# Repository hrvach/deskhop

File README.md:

# DeskHop - Fast Desktop Switching

Did you ever notice how, in the crazy world of tech, there's always that one quirky little project trying to solve a problem so niche that its only competitors might be a left-handed screwdriver and a self-hiding alarm clock?

I use two different computers in my daily workflow and share a single keyboard/mouse pair between them. Trying several USB switching boxes found on Amazon made me realize they all suffer from similar issues - it takes a while to switch, the process is quite clumsy when trying to find the button and frankly, it just doesn't get any better with time.

All I wanted was a way to use a keyboard shortcut to quickly switch outputs, paired with the ability to do the same by magically moving the mouse pointer between monitors. This project enables you to do both, even if your computers run different operating systems!

## Features

- Completely **[free and open source](https://certification.oshwa.org/de000149.html)**
- No noticeable delay when switching
- Simply drag the mouse pointer between computers
- No software installed
- Affordable and obtainable components (<15€)
- 3D printable snap-fit case
- Full Galvanic isolation between your outputs
- Works with Linux, macOS and Windows

[User Manual](misc/user-manual.pdf) is now available

------

## How it works

The device acts as an intermediary between your keyboard/mouse and the computer, establishing and maintaining connections with both computers at once. Then it chooses where to forward your mouse and keystrokes to, depending on your selection. Keyboard follows the mouse and vice versa, so just dragging the mouse to the other desktop will switch both.

## Mouse

To get the mouse cursor to magically jump across, the mouse hid report descriptor was changed to use absolute coordinates and then the mouse reports (that still come in relative movements) accumulate internally, keeping the accurate tally on the position.

When you try to leave the monitor area in the direction of the other monitor, it keeps the Y coordinate and swaps the maximum X for a minimum X, then flips the outputs. This ensures that the cursor seamlessly appears at the same height on the other monitor, enhancing the perception of a smooth transition.

<p align="center"> Dragging the mouse from Mac to Linux automatically switches outputs. </p>

------

The actual switch happens at the very moment when one arrow stops moving and the other one starts.

## Keyboard

Acting as a USB Host and querying your keyboard periodically, it looks for a preconfigured hotkey in the hid report (usually Ctrl + Caps Lock for me). When found, it will forward all subsequent characters to the other output.

To have a visual indication which output you are using at any given moment, you can repurpose keyboard LEDs and have them provide the necessary feedback.

It also remembers the LED state for each computer, so you can pick up exactly how you left it.

## How to build

To avoid version mismatch and reported path issues when building, as well as to save you from having to download a large SDK, the project now bundles minimal pico sdk and tinyusb.

On a Debian/Ubuntu systems, make sure to install these:

```shell
apt update
apt install \
    build-essential \
    cmake \
    gcc-arm-none-eabi \
    libnewlib-arm-none-eabi \
    python3
```

You should be able to build by running:

```shell
cmake -S . -B build
cmake --build build
```

additionally, to rebuild web UI check webconfig/ and execute ```./render.py```, you'll need jinja2 installed.

An alternative can be to use docker via 'docker compose' or 'docker-compose':
```
docker-compose -f misc/docker.yml run --rm build_container
```
This ensures reproducible builds.

To rebuild the disk, check disk/ folder and run ```./create.sh```, tweak to your system if needed. You'll need **dosfstools** (to provide mkdosfs),

## Using a pre-built image

Alternatively, you can use the [pre-built images](https://github.com/hrvach/deskhop/releases). Since version 0.6 there is only a single universal image. You need the .uf2 file which you simply copy to the device in one of the following ways:

## Upgrading firmware

**Option 1** - (firmware 0.6 and later) Put the device in "config mode" by simultaneously pressing **left ctrl + right shift + c + o**. Device your keyboard is plugged into will reboot and turn into a USB drive called "DESKHOP". All you need to do is copy the .uf2 file to it. Once image is verified, device will flash and reboot, then proceed to upgrade the other board. During this operation the led will blink. Once it's done, it will write flash and reboot, completing the operation.

_Note_ - This is not an actual generic USB drive, you can't use it to copy files to it.

**Option 2** - Using the ROM bootloader - hold the on-board button while connecting each Pico and copy the uf2 to the flash drive that appears. Images later than 0.6 support holding the button without having to fiddle around the power supply, but the "hold button while plugging" should always work, regardless of device state.

**Option 3** - CDC Flash Command (Debug builds only) - If the firmware was built with `DH_DEBUG_CDC_FLASH=ON`, you can trigger bootloader mode via CDC serial command:
```shell
echo -n 'flash' > /dev/tty.usbmodem11104
```
This immediately resets the device into bootloader mode where it appears as "RPI-RP2" drive. This feature is intended for development workflows.

## Misc features

### Mouse slowdown

Ever tried to move that YT video slider to a specific position but your mouse moves too jumpy and suddenly you are moving your hand super-carefully like you're 5 and playing "Operation" all over again?

**Press right CTRL + right ALT** to toggle a slow-mouse mode. The mouse pointer will slow down considerably, enabling you to get the finer precision work done and still have your mouse moving normally by quickly pressing the same keys again.

### Switch Lock

If you want to lock yourself to one screen, use ```RIGHT CTRL + K```.
This will make sure you won't accidentally leave your current screen. To turn off, press the same key combo again.

### Wrap Around

**Off by default**, turned on with the Wrap Around checkbox in the web config. Pushing the mouse past the outer edge of your outermost screen takes it to the far edge of the other computer's outermost screen, so you can keep moving in one direction and cycle between the two. The jump threshold applies here too. On Windows with more than one screen, the wrap only meets the far edge with acceleration off, Windows at its default pointer speed without Enhance pointer precision, Speed X at 32767 divided by the screen width (rounded down) and Speed Y at 32767 divided by the height.

### Lock Both Screens

You can lock both computers at once by using ```RIGHT CTRL + L```.
To make use of this feature, first set up the OS for each output in config (since the shortcuts are different).

### Gaming Mode

If you're gaming, there is a chance your game might not work properly with absolute mouse mode. To address that issue, a **gaming mode** is introduced, toggled by ```LEFT CTRL + RIGHT SHIFT + G```. When in gaming mode, you are locked to the current screen and your mouse behaves like a standard relative mouse. This should also fix various virtual machine issues, currently unsupported operating systems etc.

### Screensaver

Supposedly built in to prevent computer from entering standby, but truth be told - it is just fun to watch. **Off by default**, will make your mouse pointer bounce around the screen like a Pong ball. When enabled, it activates after a period of inactivity defined in user config header and automatically switches off as soon as you send any output towards that screen.

Potential usage example - I have a buggy USB dock that won't resume video from standby, so not allowing it to sleep can be a handy workaround.

## Hardware

[The circuit](schematics/DeskHop_v1.1.pdf) is based on two Raspberry Pi Pico boards, chosen because they are cheap (4.10 € / pc), can be hand soldered and most suppliers have them in stock.

The Picos are connected using UART and separated by an Analog Devices ADuM1201 dual-channel digital isolator (~3€) or a much cheaper, faster and pin-compatible TI ISO7721DR (~1.5€) which is the preferred choice.

While they normally don't have support for dual USB, thanks to an [amazing project](https://github.com/sekigon-gonnoc/Pico-PIO-USB) where USB is implemented using the programmable IO wizardry found in RP2040, there is support for it to act both as an USB host and device.

## PCB [updated]

To keep things as simple as possible for DIY builds, the traces were kept on one side and the number of parts kept to a minimum.

USB D+/D- differential lines should be identical in length, but they are slightly asymmetrical on purpose to counter the length difference on the corresponding GPIO traces PICO PCB itself, so the overall lengths should match.

Zd (differential impedance) is aimed as 90 ohm (managed to get ~107, close enough :)).

The thickness is designed to be 1.6 mm for snap-fit to work as expected.

There are 2 versions of the PCB (no major differences for the user). Original (v1.0) is easier to solder and assemble, while v1.1 offers some upgrades like:

- added ESD protection (TPD4E1U06DBVR)
- added VBUS capacitor for the keyboard/mouse connectors
- silkscreen orientation markings
- holes for clone boards with headers pre-soldered and easier alignment
- USB 27 ohm resistors

  This version is slightly more difficult to hand solder due to the small transient voltage suppressor IC and 0805 resistors, but it's totally doable. TVS can in theory be omitted (not advised) and it will still work.

Upcoming - board with bare rp2040s that doesn't need Picos, is smaller and more convenient.

## Case

Since I'm not very good with 3d, the case is [simple and basic](case/) but does the job. It should be easy to print, uses ~33g of filament and takes a couple of hours.

Horizontal PCB movements are countered by pegs sliding through holes and vertical movements by snap-fit lugs on the sides - no screws required. The case was given a slight redesign to feature the logo and two additional snap-fit lugs, so it provides a better seal.

Micro USB connectors on both boards are offset from the side of the case, so slightly larger holes should allow for cables to reach in.

The lid is of a snap-fit design, with a screwdriver slot for opening. The markings on top are recessed and can be finished with e.g. crayons to give better contrast (or simply left as-is).

## Bill of materials

<details closed>
  <summary>Click here to view original PCB v1.0 BOM</summary>

| Component          | Qty | Unit Price / € | Price / €|
|--------------------|-----|----------------|----------|
| Raspberry Pi Pico  | 2   | 4.10           | 8.20     |
| ADuM1201BRZ        | 1   | 2.59           | 2.59     |
| Cap 1206 SMD 100nF | 2   | 0.09           | 0.18     |
| USB-A PCB conn.    | 2   | 0.20           | 0.40     |
| Headers 2.54 1x03  | 2   | 0.08           | 0.16     |
|                    |     |                |          |
|                    |     |          Total | 11.53    |

TI ISO7721DR can be used instead of the ADuM - it's pin-compatible, much cheaper and with better specs.

</details>

### PCB v1.1

| Component      | Part                | Qty | Unit Price / € | Price / €|
|----------------|---------------------|-----|----------------|----------|
|     U1, U2     | Raspberry Pi Pico   | 2   | 4.10           | 8.20     |
|     J1, J4     | USB-A PCB conn.     | 2   | 0.20           | 0.40     |
|       U4       | TI ISO7721DR        | 1   | 1.40           | 1.40     |
|                | (**OR** ADuM1201BRZ)|     |                |          |
|     C1, C2     | Cap 0805 SMD 100nF  | 2   | 0.09           | 0.18     |
| R1, R2, R3, R4 | Res 0805 SMD 27ohm  | 4   | 0.03           | 0.12     |
|     U3, U5     | TPD4E1U06DBVR       | 2   | 0.31           | 0.62     |
|     C3, C4     | Cap 4.7uF SMD 0805  | 2   | 0.07           | 0.14     |
|     J2, J3     | Headers 2.54 1x03   | 2   | 0.08           | 0.16     |
|                |                     |     |                |          |
|                |                     |     |          Total | 11.22    |

USB-A connector can be Molex MX-67643-0910 or a cheaper/budget one that shares the same dimensions.

Additional steps:

- making the PCB ([Gerber provided](pcb/), choose 1.6 mm thickness)
- 3d printing the case ([stl files provided](case/), ~33g filament)

## Assembly guide

If you have some experience with electronics, you don't need this. However, some of you might not, and in that case this video might help guide you through the process. Please note, after soldering you should clean the flux from the PCB to prevent corrosion.

The standard process to do that is using isopropyl alcohol and an old toothbrush. But guess what? I'm not putting my old toothbrush online, so you'll just have to improvise that part :)

[NOTE] The video assembly guide covers pcb v1.0. The revised version is very similar and the procedure is basically the same.

## Usage guide

### Keyboard shortcuts - (fw versions 0.68+)

_Config_:

- ~~```Left Shift```~~ ```Left Ctrl + Right Shift + C + O``` - enter config mode
- ```Right Shift + F12 + D``` - remove flash config
- ```Right Shift + F12 + Y``` - save screen switch offset

_Usage_:

- ```Right CTRL + Right ALT``` - Toggle slower mouse mode
- ```Right CTRL + K``` - Lock/Unlock mouse desktop switching
- ```Right CTRL + L``` - Lock both outputs at once (set output OS before, see shortcuts below)
- ~~```Left Shift```~~ ```Left CTRL + Right Shift + G``` - Toggle gaming mode (lock to screen, act as standard mouse)
- ```Left CTRL + Right Shift + S``` - Enable screensaver
- ```Left CTRL + Right Shift + X``` - Disable screensaver
- ```Left CTRL + Caps Lock``` - Switch between outputs

Note: some keyboards don't send both shifts at the same time properly, that's why the shortcut was changed - to work for everyone. Apologies for the confusion.

### Switch cursor height calibration

This step is not required, but it can be handy if your screens are not perfectly aligned or differ in size. The objective is to have the mouse pointer come out at exactly the same height.

Just park your mouse on the LARGER screen at the height of the smaller/lower screen (illustrated) and press ```Right Shift + F12 + Y```. Your LED (and caps lock) should flash in confirmation.

Repeat for the bottom border (if it's above the larger screen's border). This will get saved to flash and it should keep this calibration value from now on.

### Multiple screens per output

Windows and Mac have issues with multiple screens and absolute positioning, so workarounds are needed (still experimental). There is a better workaround under construction, but for now you have to set the operating system for each output and number of screens.

Your main screens need to be in the middle, and secondary screen(s) on the edges. To configure the actual options, open the web configuration page for your device.

### Web configuration mode

Starting with fw 0.6, an improved configuration mode is introduced. To configure your device, follow these instructions:

1. Press Left Ctrl + Right Shift + C + O - your device will reboot and enter configuration mode (on the side your keyboard is plugged into). LED will keep blinking during the configuration session.

1. A new USB drive will appear named "DESKHOP" with a single file, config.htm

1. Open that file with Chromium / Chrome. Unfortunately FF is not supported right now, since they avoid implementing WebHID.

1. Click connect and allow deskhop device to pair.

1. Configure the options as you wish and click save to write to device.

1. Click "exit" in the menu to leave configuration mode for added safety.

<details closed>
  <summary>Linux doesn't see device? Click here.</summary>

**Q**: Chromium on Linux doesn't work.

**A**: You probably need to tweak /dev permissions or create a corresponding udev rules file and make sure your user is in the right group, like so:

/etc/udev/rules.d/99-deskhop.rules

```plain
KERNEL=="hidraw*", SUBSYSTEM=="hidraw", ATTRS{idVendor}=="1209", ATTRS{idProduct}=="c000", GROUP="plugdev", MODE="0660"
```

</details><br />

**Q**: Why not simply create a nice online web page like Via instead of dealing with this weird USB drive thing?

**A**: Loading javascript from a random online location that interacts with your input devices is a potential security risk. The configuration web page is local only and nothing is ever loaded externally.

Please note the config web page is not "weird" because of deliberate obfuscation - it's self-decompressing due to very limited storage. Entire source is 100% open and a part of this repo. You are encouraged to rebuild everything yourself.

### Functional verification

When you connect a new USB peripheral, the board will flash the led twice, and instruct the other board to do the same. This way you can test if USB and outgoing communication works for each board.

Do this test by first plugging the keyboard on one side and then on the other. If everything is OK, leds will flash quickly back and forth in both cases.

## Security and Safety

Some features are missing on purpose, despite the fact it would make the device easier to use or simpler to configure. Here is a quick breakdown of these decisions:

- There is no copy-paste or _any_ information sharing between systems. This prevents information leakage.
- No webhid device management without explicit user consent. No inbound connectivity from the output computers, with the only exception of standard keyboard LED on/off messages and hard limited to 1 byte of data.
- No FW upgrade triggering from the outputs. Only explicit and deliberate user action through a special keyboard shortcut may do that.
- No plugged-in keyboard/mouse custom endpoints are exposed or information forwarded towards these devices. Their potential vulnerabilities are effectively firewalled from the computer.
- No input history is allowed to be retained.
- No device-initiated keystrokes, for any reason. Only thing that comes out is what you type/trigger.
- Outputs are physically separated and galvanically isolated with a minimal isolation voltage of 2kV.
- All packets exchanged between devices are of fixed length, config options transferred are limited to a short list. Most options are read-only. Cross-device firmware upgrades can be disabled.
- There is no bluetooth or wifi, networking, Internet access, etc.
- No connected computer is considered trusted under any circumstances.
- Configuration mode is automatically disabled after a period of inactivity.
- Entirety of the code is open source, without any binary blobs and thoroughly commented to explain its purpose. I encourage you to never trust anyone and always make sure you know what you are running by doing a manual audit.

This still doesn't guarantee anything, but I believe it makes a reasonable set of ground rules to keep you safe and protected.

## FAQ

1. I just have two Picos, can I do without a PCB and isolator?

   _Sure. Having an isolator is recommended but it should work without it._

1. What happens if I have two different resolutions on my monitors?

   _The mouse movement is done in abstract coordinate space and your computer figures out how that corresponds with the physical screen, so it should just work._

1. Where can I buy it?

   _I'm not selling anything, this is just a personal, non-commercial hobby project._

   _**UPDATE 1**: It seems you can order it in QTY of 1 (for either PCB, assembled PCB or a fully assembled device) from [Elecrow if you follow this link](https://www.elecrow.com/deskhop-fast-desktop-switching.html)_
   _As reported by users, your **board will arrive blank** and you have to write the firmware yourself._

   _**UPDATE 2**: I never asked Elecrow for anything, but a couple of days ago they offered to sponsor the project with a small budget that will be used for future board prototyping. Since my goal is to create a better board with more than 2 outputs etc, I believe prototyping services might be beneficial to the project._

1. When the active screen is changed via the mouse, does the keyboard follow (and vice versa)?

   _Yes, the idea was to make it behave like it was one single computer._

1. Will this work with keyboard/mouse combo dongles, like the Logitech Unifying receiver?

   _It should work. After a recent FW update, support for combo receivers should be much better._

1. Will this work with wireless mice and keyboards that have separate wireless receivers (one for the mouse, another for the keyboard)?

   _It should work - tried an Anker wireless mouse with a separate receiver and that worked just fine._

1. I have issues with build or compilation

   _Check out the [Troubleshooting Wiki](https://github.com/hrvach/deskhop/wiki/Troubleshooting) that might have some answers._

## Software Alternatives

There are several software alternatives you can use if that works in your particular situation.

1. [Barrier](https://github.com/debauchee/barrier) - Free, Open Source
1. [Input Leap](https://github.com/input-leap/input-leap) - Free, Open Source
1. [Synergy](https://symless.com/synergy) - Commercial
1. [Mouse Without Borders](https://www.microsoft.com/en-us/garage/wall-of-fame/mouse-without-borders/) - Free, Windows only
1. [Universal Control](https://support.apple.com/en-my/HT212757) - Free, Apple thing

## Shortcomings

- Windows 10 broke HID absolute coordinates behavior in KB5003637, so you can't use more than 1 screen on Windows (mouse will stay on the main screen). There is an experimental workaround with a better one on the way.
- Code needs cleanup, some refactoring etc.
- Not tested with a wide variety of devices, I don't know how it will work with your hardware. There is a reasonable chance things might not work out-of-the-box.
- Advanced keyboards (with knobs, extra buttons or sliders) will probably face issues where this additional hardware doesn't work.
- Super-modern mice with 300 buttons might see some buttons not work as expected.
- NOTE: **Both computers need to be connected and provide power to the USB for this to work** (as each board gets powered by the computer it plugs into). Many desktops and laptops will provide power even when shut down nowadays. If you need to run with one board fully disconnected, you should be able to use a USB hub to plug both keyboard and mouse to a single port.
- MacOS has issues with more than one screens, latest firmware offers an experimental workaround that fixes it.

## Progress

So, what's the deal with all the enthusiasm? I can't believe it - please allow me to thank you all! I've never expected this kind of interest in a simple personal project, so the initial features are pretty basic (just like my cooking skills) and mostly cover my own usecase. Stay tuned for firmware updates that should bring wider device compatibility, more features and less bugs. As this is a hobby project, I appreciate your understanding for being time-constrained and promise to do the best I can.

Planned features:

- Better workarounds for multiscreen windows and macos
- Transparent / Gaming mode
- Support for more than 2 outputs
- Improvements on the configuration UI
- ... and more!

Working on a _lite_ version which provides basic functionality with just a single Pico W board, lowering the cost even further and enabling you to try it out even with no added hardware or PCB.

Mouse polling should now work at 1000 Hz (the dips in the graph is my arm hurting from all the movement :-)):

## Sponsor / donate

I'm NOT doing this for profit or any other reason except to try and help people by creating a better working environment for everyone.
If you want to support the project further, please consider making a small donation towards a charity like **Doctors Without Borders**.

Please allow me to thank everyone who helped or considering it!

## Disclaimer

I kindly request that anyone attempting to build this project understands and acknowledges that I am not liable for any injuries, damages, or other consequences. Your safety is important, and I encourage you to approach this project carefully, taking necessary precautions and assuming personal responsibility for your well-being throughout the process. Please don't get electrocuted, burned, stressed or angry. Have fun and enjoy!

Happy switchin'!

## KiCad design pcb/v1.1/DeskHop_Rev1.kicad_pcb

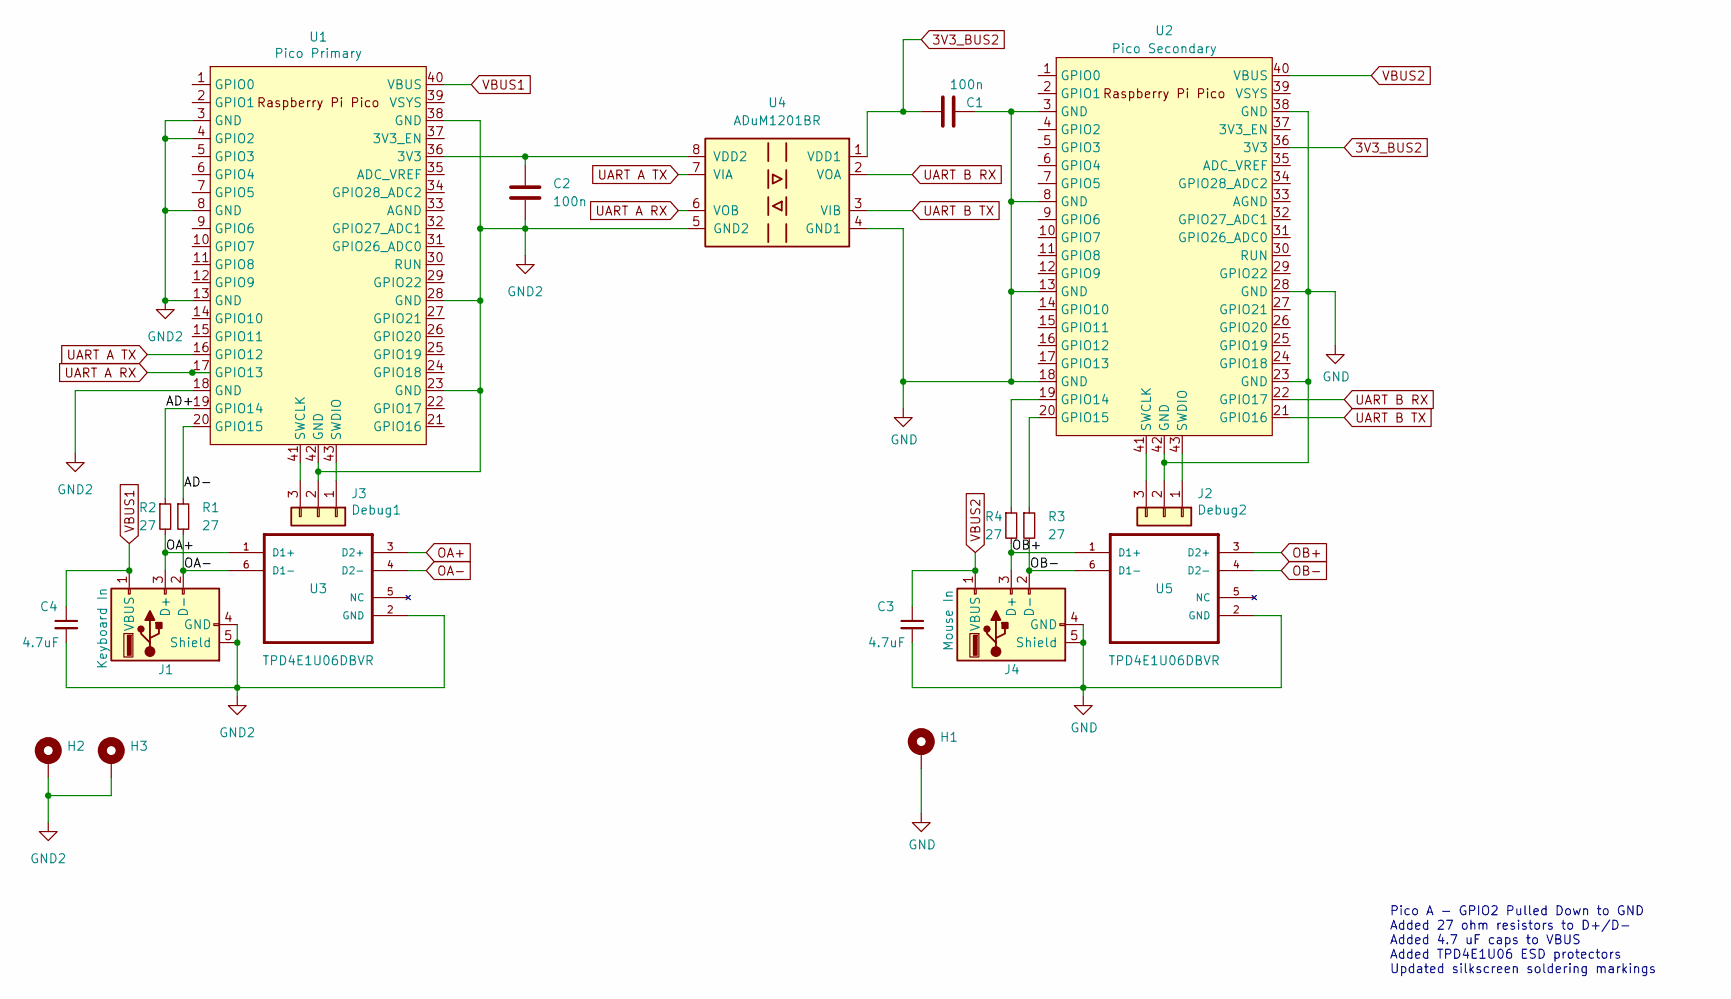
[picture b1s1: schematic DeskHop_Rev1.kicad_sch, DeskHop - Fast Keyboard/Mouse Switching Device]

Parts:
C1, C2: 100n; C_0805_2012Metric
C3, C4: 4.7uF; C_0805_2012Metric
H1, H2, H3: MountingHole_Pad; MountingHole_2.7mm_M2.5_Pad_TopBottom
J1: Keyboard In; USB_A_Molex_67643_Horizontal
J2: Debug2; PinHeader_1x03_P2.54mm_Vertical
J3: Debug1; PinHeader_1x03_P2.54mm_Vertical
J4: Mouse In; USB_A_Molex_67643_Horizontal
R1, R2, R3, R4: 27; R_0805_2012Metric
U1: Pico Primary; RPi_Pico_SMD_TH
U2: Pico Secondary; RPi_Pico_SMD_TH
U3, U5: TPD4E1U06DBVR
U4: ADuM1201BR; SOIC-8_3.9x4.9mm_P1.27mm

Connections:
3V3_BUS2: C1.1, U2.36 (3V3), U4.1 (VDD1)
/AD+: R2.1, U1.19 (GPIO14)
/AD-: R1.1, U1.20 (GPIO15)
GND: C1.2, C3.2, H1.1, J2.2, J4.4 (GND), J4.5 (Shield), U2.3 (GND), U2.8 (GND), U2.13 (GND), U2.18 (GND), U2.23 (GND), U2.28 (GND), U2.38 (GND), U2.42 (GND), U4.4 (GND1), U5.2 (GND)
GND2: C2.2, C4.2, H2.1, H3.1, J1.4 (GND), J1.5 (Shield), J3.2, U1.3 (GND), U1.4 (GPIO2), U1.8 (GND), U1.13 (GND), U1.18 (GND), U1.23 (GND), U1.28 (GND), U1.38 (GND), U1.42 (GND), U3.2 (GND), U4.5 (GND2)
unnamed: J2.1, U2.43 (SWDIO)
unnamed: J2.3, U2.41 (SWCLK)
unnamed: J3.1, U1.43 (SWDIO)
unnamed: J3.3, U1.41 (SWCLK)
unnamed: C2.1, U1.36 (3V3), U4.8 (VDD2)
unnamed: R4.1, U2.19 (GPIO14)
unnamed: R3.1, U2.20 (GPIO15)
OA+: J1.3 (D+), R2.2, U3.1 (D1+), U3.3 (D2+)
OA-: J1.2 (D-), R1.2, U3.4 (D2-), U3.6 (D1-)
OB+: J4.3 (D+), R4.2, U5.1 (D1+), U5.3 (D2+)
OB-: J4.2 (D-), R3.2, U5.4 (D2-), U5.6 (D1-)
UART A RX: U1.17 (GPIO13), U4.6 (VOB)
UART A TX: U1.16 (GPIO12), U4.7 (VIA)
UART B RX: U2.22 (GPIO17), U4.2 (VOA)
UART B TX: U2.21 (GPIO16), U4.3 (VIB)
VBUS1: C4.1, J1.1 (VBUS), U1.40 (VBUS)
VBUS2: C3.1, J4.1 (VBUS), U2.40 (VBUS)

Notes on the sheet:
Pico A - GPIO2 Pulled Down to GND Added 27 ohm resistors to D+/D- Added 4.7 uF caps to VBUS Added TPD4E1U06 ESD protectors Updated silkscreen soldering markings

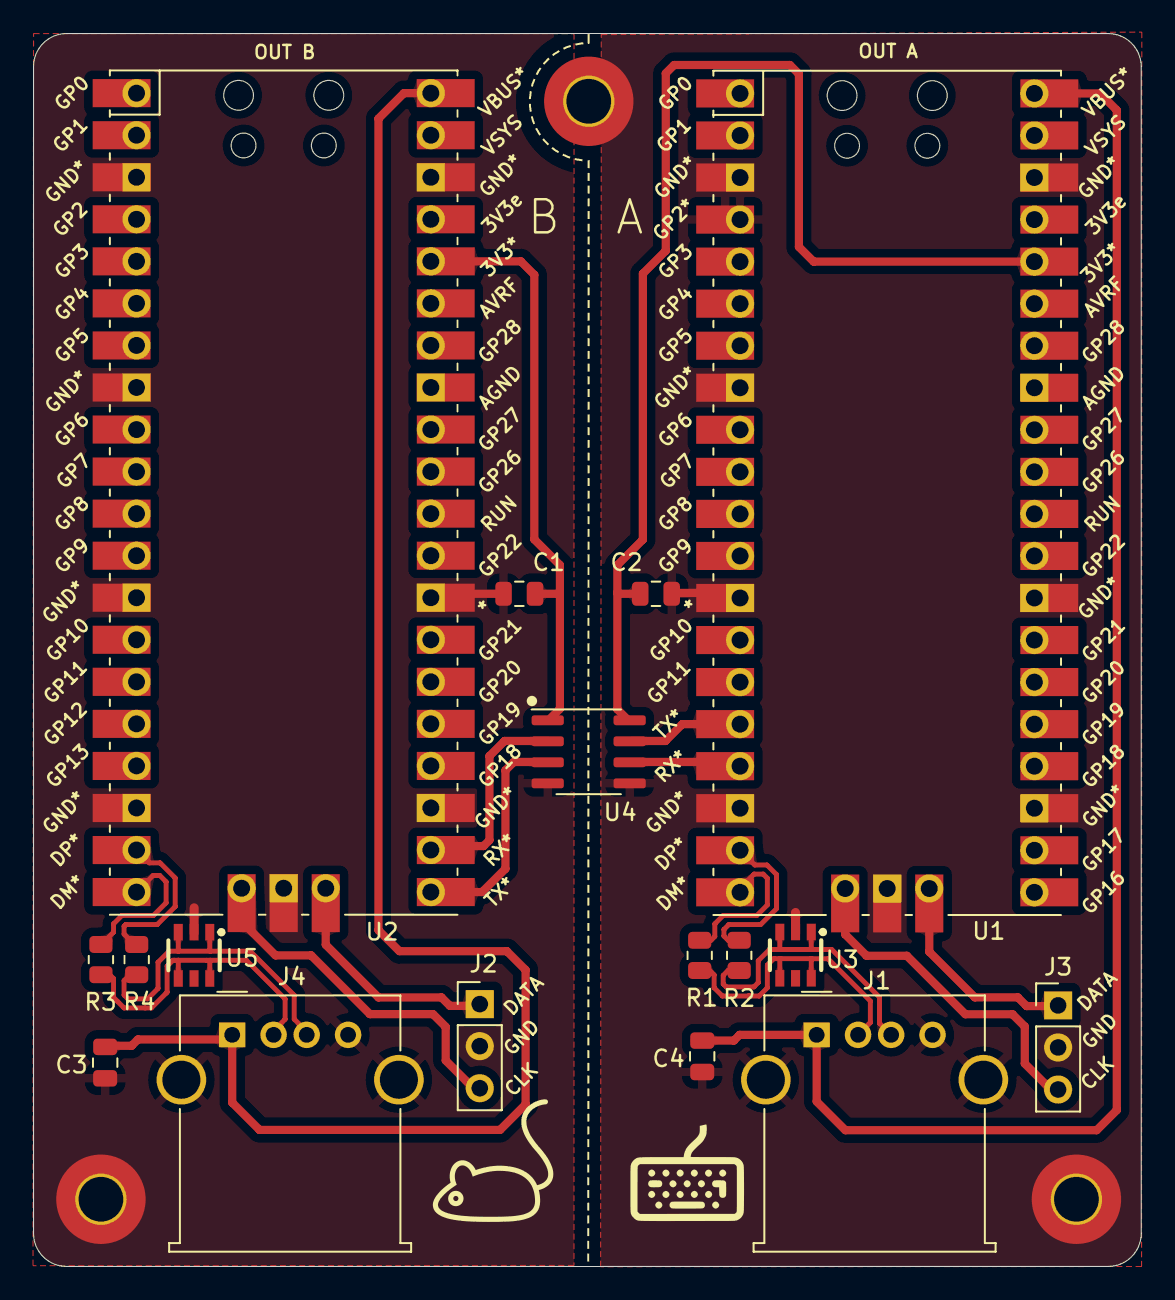
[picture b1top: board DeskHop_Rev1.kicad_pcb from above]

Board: 2 copper layers, 66.9 x 74.5 mm, 20 parts (0 on the bottom side), 22 nets.

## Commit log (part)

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2023-12-26 Updating USB-A part number.
2023-12-26 Updated FAQ section
2023-12-29 README update
2023-12-29 [README.md] Use `cmake --build` and source location flags to simplify and cross-platform configuring & building
2023-12-30 Adding software alternatives
2024-01-03 New features, bugfixes and optimizations
    Some of the features implemented in this release are:
    - TinyUSB used to handle HOST management as well
    - USB hub support (tried an ancient one and it worked)
    - Early and buggy support for mouse on the keyboard side
    but have no unified usb receivers to test
    - Rudimentary HID report descriptor parsing, support for
2024-01-03 Updating docs
2024-01-06 Updated known bugs, progress and software alternatives in README
2024-01-11 Bugfixes and improvements: ==========================
    Added 1000 Hz polling.
    (Hopefully) fixed Logitech mouse issues
    Removed special treatment for 12 and 16-bit mice
    Increased mouse queue size
    Increased current allowance from 100mA to 500mA
    Allow mouse to wake up a suspended host
2024-01-13 Added proper USB VID/PID
    Kindly assigned by the Raspberry Pi foundation, the project got its own
    VID/PID so removing the current "test" one and adding this one. No other
    changes.
2024-01-16 Change board type to pico_w
2024-01-16 Disable LED code for pico_w
2024-01-16 Typo
2024-01-16 README formatting
2024-01-27 Minor updates and bugfixes
    - Mouse movements should be smoother on the other Pico
    - Reworked CMakeLists with foreach to avoid duplication
    - Increased WDT timeout
2024-03-18 Screensaver features:
    * Per-output enablement
    * Maximum time
    * Enable only when output is inactive
    Closes #66.
2024-03-22 Features and fixes
    - Auto switch-lock when dragging or resizing windows.
    * This was super annoying for me, resizing a window and you
    get too close to the left border, making it shrink suddenly.
    Now if you drag while holding a mouse button pressed, it will
    not switch.
    - Added Mac OS multiple desktop workaround
2024-03-24 - add windows workaround - add mouse acceleration (configurable in user_config.h) - add keyboard shortcuts for output configuration - after several reports, bundling pico-sdk and tinyusb to simplify 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
2024-03-27 Add TinyUSB DFU support (from Pico SDK).
2024-03-27 Inital DFU support.
    * Adds "DFU Runtime" support while the application is in "HID" (normal)
    mode; this is controllable in user_config.h.
    * Adds "DFU" mode for the application, which avoids most normal setup
    steps and prepares the device for firmware/config upload or download.
    * Adds "DFU DETACH" support, allowing a DFU tool to trigger a reboot
    into "DFU" mode (with a 30 second timeout to return to "HID" mode).
2024-03-31 Minor fix and update binaries.
2024-04-02 fix: lets not assume remapped keys
    fixes https://github.com/hrvach/deskhop/issues/82
2024-04-04 Add 'reboot_board' utility function.
2024-04-04 Cancel the DFU '30 second timeout' once a transfer has begun.
2024-04-11 chore: fix screenlock
    Shortcut is always received local to the device the keyboard is
    connected to. Send command to all others.
2024-06-12 add config MOUSE_PARKING_POSITION
2024-06-18 Wake up on keyboard events
2024-06-23 Updated README with Elecrow link
2024-06-27 Small compile bugfix
2024-06-30 Added a special case for mousekeys in QMK keyboard
2024-07-15 Adding simple jitter screensaver mode
2024-07-30 DeskHop v0.61 - Promoted RC to Stable
    - Single unified firmware binary
    - Improved support for NKRO keyboards
    - Report mode default for keyboard port
    - Improved consumer control parser for variable
    data types (media keys should be better supported)
    - System control forwarding
2024-07-30 Adding images
2024-08-07 Added my changes to whichever main branch was there
2024-08-13 Allow dragging between monitors on same output
2024-08-18 DeskHop 0.63 (Bugfixes, small features)
    - add gaming mode (use left shift + right shift + G to toggle)
    - rework HID queue, smoother operation of rotary dials (no packets lost)
    - fix dragging across multiple screens on the same output
    - improve read reliability for UI
    - move default keyboard hotkey for output switching to LCtrl + Caps Lock
    - change default X/Y speed to match 16:9 geometry
2024-08-26 Updating README.md with the keyboard shortcut changes.
2024-08-26 Updated donation link to Doctors Without Borders
2024-09-14 Update PCB to fix the GND pad on board A pin 3.
2024-09-30 Changes to LED
    Some changes to web
2024-10-02 Update back wrong stuff
2024-10-02 Company Change
2024-10-02 Quick fix
2024-10-02 Changes to build
2024-10-02 test changes to name branding
2024-10-02 svg reuse
2024-10-31 DeskHop v0.66 - Fixed a bug with special keys parsing
2024-10-31 Bump FW Version
2024-11-22 Unbreak relative mouse mode by adding pan to descriptor
2024-11-23 Bump FW version to 0.67
2024-11-25 DeskHop v0.68 - Wrote a "proper" user manual - Added screensaver shortcuts - Modified descriptor from 5+3 buttons to 8 buttons - Added OSHW cert to docs - Bumped bootsel detection to debug version - 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
2024-11-25 Fix oshw logo #2
2024-11-25 Tweak Readme
2024-11-27 Tweak macos screen switch helper
    - Increase relative mouse movement to over one screen pixel in most
    resolutions
    - Extract MacOS desktop switch helper to its own function
    - Clean up unused parameters in top-level desktop switch
2024-12-04 Use relative mouse reports for jitter screensaver mode
2024-12-04 Fix screensaver issue with rapid movement.
2024-12-06 fix: doubled move_x accounting
2024-12-09 Allow buttons without pointer usage
2024-12-10 fix: screensaver should not wake host from sleep
2024-12-20 Small ignores
2025-01-08 Enforce 64 bit precision on times
    While building with SCREENSAVER_A_MAX_TIME_SEC 3600, I got an error:
    warning: integer overflow in expression of type 'int' results in '-694967296'
    This should fix that.
2025-01-09 clean up comment formats to be uniform
2025-01-09 swap tabs for spaces
2025-01-09 add initial editorconfig
2025-01-09 Apply markdown linting to README
    - uniform italics and bold
    - uniform lists
    - various indentation fixes
    - improved image alt text
    - type hint all multiline code boxes
2025-01-09 add Dockerfile
2025-01-17 Imported project into VS Code with Raspberry Pi Pico Extension
2025-01-17 Add docker build method and update readme
2025-01-18 Added timeout based on board's heartbeat Heartbeat increased from 1Hz to 10Hz for better responsiveness Timeout fixed to 2s, this should be added to the configuration
2025-01-19 Adding Docker as a supported build method.
2025-01-19 Fixed compilation issues with older GCC.
    Issue reported in #196.
2025-01-27 Add support for device serial numbers. This should resolve #212
2025-02-07 Build with GitHub Actions
2025-02-07 Bugfixes and compatibility enhancements. - Fix non-aligned nkro bit array parsing. - Small refactoring of multiple report ID parsing
2025-02-09 Various bugfixes and improvements - Firmware version and checksum were incorrectly parsed. Welp, this is embarassing - struct defined u32, but struct.pack in Python helper packed it as 16-bit. ->> Mi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
2025-02-14 keep button state when report does not contain buttons.
2025-02-14 fix transition between screens of different sizes on macos.
2025-02-16 Reconfigured CMakeLists.txt for PICO series boards
2025-02-25 Allow detection of switch needed on all four edges
2025-02-26 More properly place the cursor when switching vertically
2025-02-26 changed uart and LED pins to fit RP2040-Zero pins
2025-02-27 Updated LP Disk
2025-08-12 Add keyboard shortcut to enable the Jitter screensaver
    Add keyboard shortcut for Jitter screensaver
2025-08-17 Refactor the support for multiple keyboards a bit.
2025-08-17 Minor fixes - avoid potential buffer overflows.
2025-08-17 - Add webconfig change to display the fw version properly. - Update javascript to support swapped vendor IDs. - Bump version.
2025-10-09 Add CDC command to trigger bootloader mode when enabled.
    Add CDC RX callback that triggers bootloader when receiving "flash" command.
2025-10-10 Track HID report offsets per report ID per USB spec
    Per USB HID spec section 6.2.2.7, each report ID defines an independent
    report structure with its own bit offset tracking. Previously, offsets
    were reset when encountering a new report ID or at collection boundaries,
    causing incorrect parsing of descriptors with multiple reports.
    Changes:
    - Add report_offset_map_t to map report IDs to their offsets
2025-12-04 Add gaming mode features with edge switching support
2025-12-05 Enhance gaming mode edge switching with vertical movement checks and configuration refinements.
2026-01-07 use native browser gzip decompression; reduce config.htm from 13984 to 9980 bytes
2026-01-10 sync firmware A->B if the firmware versions are the same, but CRC differs; common during development.
2026-01-10 mount config drive to the currently active device rather than whatever device the keyboard is connected to.
2026-01-10 Add device_t.mouse_connected field.
2026-01-10 remap when transitioning between intracomputer screens
2026-01-10 Add import/export json config to webui
2026-01-10 reset macos cursor to screen 1 when transitioning to that computer.
2026-01-11 Always send clicks over the relative mouse (iPad does not support clicks from the Absolute Positioning interface).
2026-01-11 add usage tips to the config webui
2026-01-11 Add press-and-hold for temporary output switching to leftctrl+capslock hotkey.
2026-01-11 Add config webui autoconnect logic.
2026-01-12 Fix dragging windows across macos virtual desktops
2026-01-14 add vertical monitor/computer support
2026-01-31 Fixed some copy and paste
2026-01-31 Bugfixes
    - Increase number of keyboards to 5, complex / weird descriptors were seen to exhaust the limit
    - Avoid increasing num_keyboards multiple times for a single report_id (seen with Apple keyboard)
2026-04-06 Create top_with_light_pipe_holes.md
    Explanation of why and how to use the alternate case top 3D model.
2026-05-20 wording
2026-05-20 Fix mouse movement threshold and stuck drag during virtual desktop switches
2026-05-25 add hi-res scroll support
    Detect Resolution Multiplier in attached mouse's HID descriptor
    and normalize wheel/pan values to standard notch units before
    forwarding. Prevents scrolling being ~16× too fast with hi-res
    scroll devices (e.g. Endgame trackball).
2026-06-26 Fix conditional check for report length in HID report
2026-06-26 Fix comment formatting in hid_report.c
2026-06-26 - Bugfixes, range checks. - Backporting some PIO fixes for stability. - Add LED sync task and desired/actual register. Should be more reliable.
2026-06-27 Fix ramdisk mount bug.
